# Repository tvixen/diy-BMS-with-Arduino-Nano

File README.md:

## Update 12/3-2019

New PCB version 3.0.8 added. Including gerber files for PCB in .zip file.

## Update 30/11-2018
Final slave module is ready and running. Software has been updated on slaves and master. Big packs of 100 cells, has been added. 
Pictures:

## Update 13/7-2018

Arduino code for Master is uploaded. It's purly working as master, and without any debug information. But it should be plug'n play.
Arduino code for Slave is uploaded. No really debug information in code.

## Update 11/7-2018

Feel free to add comments or copy the whole project. It will be updated continuously.....
Next update will be the code for the Master and Slave.
Hardware drawings was updated to 3.0.4

-------------------------------------------------------------------------------------------------------------------------------

# Project "diyBMS with Arduino Nano" (11/7-2018)
Do it yourself battery management system to Lithium ion battery packs/cells
Inspired by Stuart Pittaway, and therefore the credit goes to him.

I was building a powerwall, and for that I needed a sort of batteri management. I have had a look at Batrium, but they was located in the US and the import would be to costly. So I found 
Stuart's project and thourght "This could work". But I was in need of a display and a precise 16bit ADC, so I found some cheap alternatives and added them to the circuit. A new PCB was now under construction.
Then I ordered the parts, and for my big surprise there were no power supply chips or ATtiny85 chips on the marked. So I decided to change the design and use what I had in the drawer. A handful of Arduino Nano.
So therefore this project is designed around the Arduino Nano with a boot sector from the Optiboot project. (no big deal of burning an ordinary Nano with Optiboot) 
The features are also a little different from the original project, as I’m not using the ESP8266 with Wifi, so there will be no transmitting data to a web interface.
Instead the slave modules can show the value of the battery pack (very precise), and the module number itself. The Master will show the status of all the modules, and also send balance commands 
to the module who is sticking out from rest of the packs/cells. + Every module will check if the voltage is over 4.200 volts and balance itself if needed. 

# The design

* One central controller and up to 24 individual cell monitoring nodes.
* The PCB is intented to be sitting in front of a batteri pack with 100.pcs 18650 cells, soldered together with fuses of 1.amp each.
* Use Arduino code, libraries and tools
* Use Arduino Nano as the Master and Slave, so a single PCB can be used as both Master or Slave. 
* Use good connection cables with low noise (twisted pairs)
* The Master will monitoring and control the slaves on the bus.
* The Slave will monitor itself, and discharge if the voltage is higer than 4.200 volts.
* Every single slave will show the pack voltage and the module number on the LED display.
* Ensure each cell voltage is isolated from other cells and that ground voltage is isolated
* Ensure communications between controller and node is isolated
* Keep the coste to a minimum and use whatever theres in the drawer.

# The code

* I did try to use as much of Stuart's origianal code as possible, but had to add a lot of stuff 
* keep it short and simple
* Try not to do inline stuff, as this can be difficult to convert to other platforms/chips

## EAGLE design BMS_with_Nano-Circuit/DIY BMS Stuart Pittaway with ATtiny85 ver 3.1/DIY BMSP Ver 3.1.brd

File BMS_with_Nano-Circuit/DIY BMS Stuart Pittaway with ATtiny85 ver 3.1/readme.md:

# 18/7-2018
New board made with smaller foot print 40*78mm, and now with holes for mounting on 3D printed holder.
Use Stuart's code for this print.

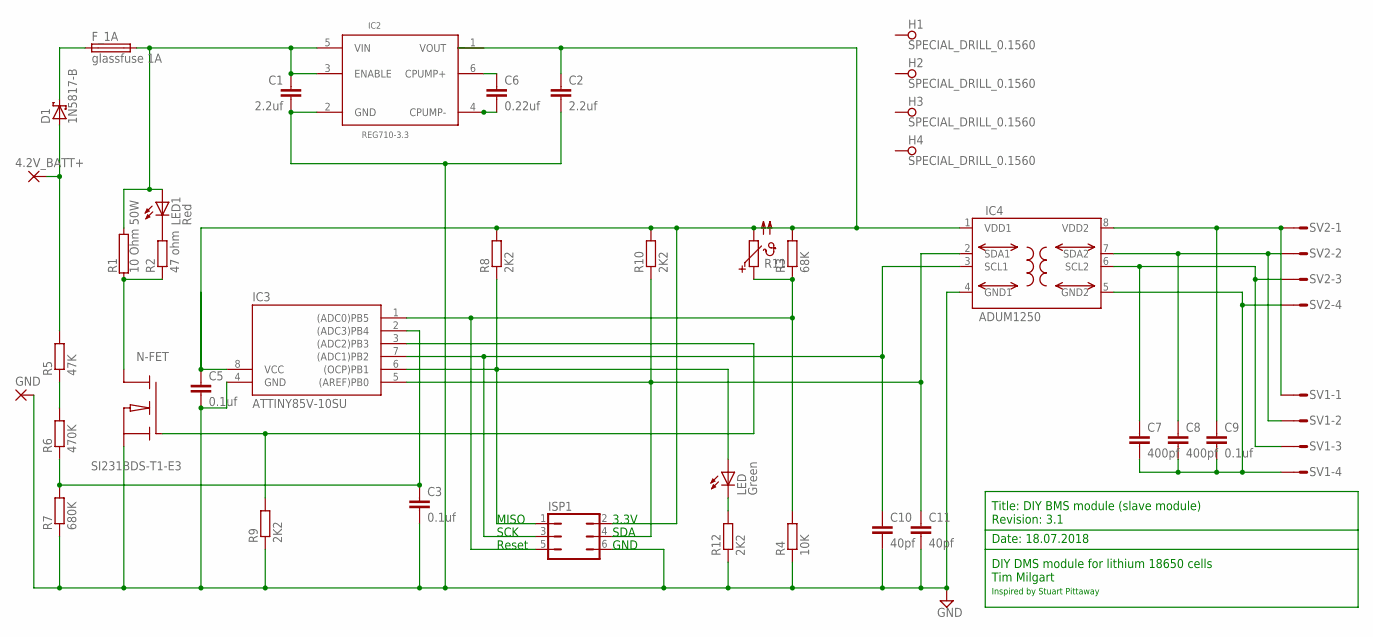
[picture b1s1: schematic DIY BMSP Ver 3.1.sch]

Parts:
4.2V_BATT+: 3,17/1,3
C1, C2: 2.2uf; C050-025X075
C3, C5, C9: 0.1uf; C050-025X075
C6: 0.22uf; C050-025X075
C7, C8: 400pf; C050-024X044
C10, C11: 40pf; C050-024X044
D1: 1N5817-B; DO41-7.6
F_1A: glassfuse 1A; PICOFUSE
GND: 3,17/1,3
H1, H2, H3, H4: SPECIAL_DRILL_0.1560; PAD_0.1560
IC2: REG710-3.3; SOT-23-6
IC3: ATTINY85V-10SU; DIL08
IC4: ADUM1250; SO8-COOL
ISP1: JP3Q
LED: Green; LED3MM
LED1: Red; LED3MM
N-FET: SI231BDS-T1-E3; SOT23
R1: 10 Ohm 50W; HPS947
R2: 47 ohm; 0207/10
R3: 68K; 0207/10
R4: 10K; 0207/10
R5: 47K; 0207/10
R6: 470K; 0207/10
R7: 680K; 0207/10
R8, R9, R10, R12: 2K2; 0207/10
R11: PTC679; P679
SV1, SV2: L04P

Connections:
GND1: C1.2, C2.2, C3.2, C5.2, C10.2, C11.2, GND.1, IC2.2 (GND), IC3.4 (GND), IC4.4 (GND1), ISP1.6, N-FET.2 (S), R4.1, R7.1, R9.1, R12.1
GND2: C7.2, C8.2, C9.2, IC4.5 (GND2), SV1.4, SV2.4
unnamed: 4.2V_BATT+.1, D1.A, R5.2
unnamed: D1.C, F_1A.1
unnamed: C8.1, IC4.7 (SDA2), SV1.2, SV2.2
unnamed: C6.1, IC2.6 (CPUMP+)
unnamed: C7.1, IC4.6 (SCL2), SV1.3, SV2.3
unnamed: IC3.3 ((ADC2)PB3), N-FET.1 (G), R9.2
unnamed: LED.K (C), R12.2
unnamed: C10.1, IC3.7 ((ADC1)PB2), IC4.3 (SCL1), ISP1.3
unnamed: C3.1, IC3.2 ((ADC3)PB4), R6.1, R7.2
unnamed: C11.1, IC3.5 ((AREF)PB0), IC4.2 (SDA1), ISP1.4, R10.1
unnamed: R5.1, R6.2
unnamed: C6.2, IC2.4 (CPUMP-)
unnamed: IC3.6 ((OCP)PB1), ISP1.1, LED.A, R8.1
unnamed: IC3.1 ((ADC0)PB5), ISP1.5, R3.1, R4.2, R11.1
unnamed: N-FET.3 (D), R1.1, R2.1
unnamed: LED1.K (C), R2.2
unnamed: C1.1, F_1A.2, IC2.3 (ENABLE), IC2.5 (VIN), LED1.A, R1.2
VDD1: C2.1, C5.1, IC3.8 (VCC), IC4.1 (VDD1), ISP1.2, R3.2, R8.2, R10.2, R11.2
VDD2: C9.1, IC4.8 (VDD2), SV1.1, SV2.1

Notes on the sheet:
Reset
SCK
MISO
SDA
3.3V
GND
Title: DIY BMS module (slave module) Revision: 3.1
Date: 18.07.2018
DIY DMS module for lithium 18650 cells Tim Milgart
Inspired by Stuart Pittaway

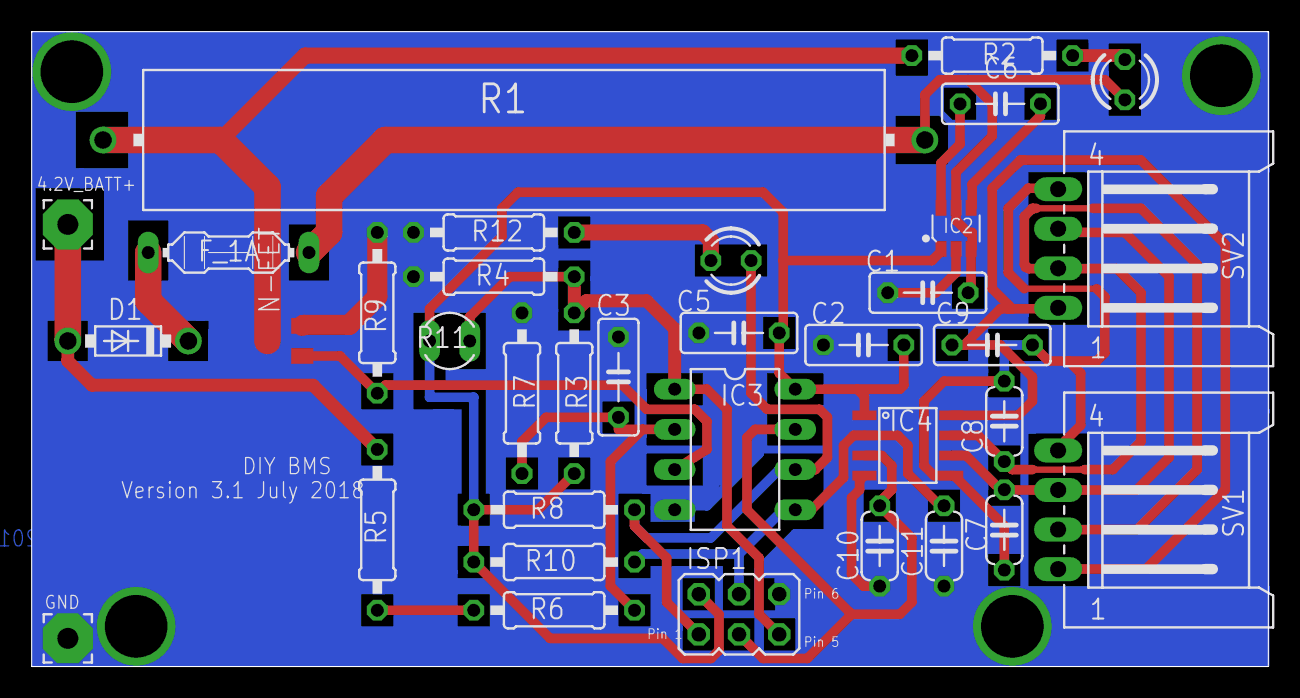
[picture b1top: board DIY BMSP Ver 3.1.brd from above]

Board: 2 copper layers, 78.2 x 40.1 mm, 39 parts (0 on the bottom side), 21 nets.

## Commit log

2018-07-11 Add files via upload
    The ATTiny85 removed
    Corrected the text angle for the display
2018-07-17 Add files via upload
    Stuart's original design, with normal resistors and caps. (the ones you have in your drawer)
2018-07-17 switched some lines
2018-07-18 Add files via upload
    New board made with smaller foot print 40*78mm, and now with holes for mounting on 3D printed holder.
2018-11-29 Add files via upload
    In this version the display has changed to SPI (5 pins) as I coulden't address 7 OLED's at the same I2C BUS.
    There's still one master (number 24) and 6 slaves. The batteri pack is now expanded to 7S100. 7 packs with 100 cells inside.
